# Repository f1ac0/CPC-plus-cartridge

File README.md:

# CPC-plus-cartridge
In this repository you will find different PCB designs and code to make a CPC-plus cartridge. The ACID chip is implemented inside a XC9536XL CPLD using the equations published by octoate : https://www.octoate.de/articles/acid-verilog-code/

Facts about this project :
- The ZIF version has a ZIF socket for DIP32 ROM SST39SF040 or W29C040, and is longer than standard cartridges
- the PLCC version can be used with PLCC SST39SF040 ROMs and its size is more standard
- They both have jumpers to select 128k, 256k or 512K cartridge ROM banks

# Disclaimer
This is a hobbyist project, it comes with no warranty and no support. Also remember that the Amstrad machines are about 30 years old and may fail because of such hardware expansions.

I publish my work under the CC-BY-NC-SA license.

If you find it useful and want to reward me : I am always looking for Amiga/Amstrad CPC hardware to repair and hack, please contact me.

# BOM
- 1x XC9536XL CPLD
- 1x DIP32/PLCC32 ROM SST39SF040 or W29C040 and appropriate socket
- 1x 3.3v LDO, either SPX3819M5-L-3-3 or XC6206P332MR
- 2x 1uF (or more) 0805 capacitors
- 4x 100nF 0805 capacitors

# Making it
Check for shorts at least between 5V, 3.3V, and GND traces before applying power !

The programming port does not need to be soldered since it needs to be programmed just once : you can just hold it in place during the few seconds required for programming.

CPLD code is generated and built into xsvf using Xilinx ISE 14.7 IDE then iMPACT. "Macrocell power setting" can be "Low" an "Slew rate" to "Slow".

There are several methods to program the XC9536XL. I personally use xsvfduino : https://github.com/wschutzer/xsvfduino

Check the alignment between the cartridge pads and connector pads inside the CPC when installing it for the first time.

# Using it
- Burn the ROM images and install the ROM. Do not burn .cpr files directly, they need to be first converted using for example "CPRTools".
- Choose the ROM to use and its size using the jumpers :
  - 512k = both jumpers vertical
  - 256k = "128" jumper vertical and "256" to select 0 or 1
  - 128k = both jumpers to select 0 or 1
- Enjoy

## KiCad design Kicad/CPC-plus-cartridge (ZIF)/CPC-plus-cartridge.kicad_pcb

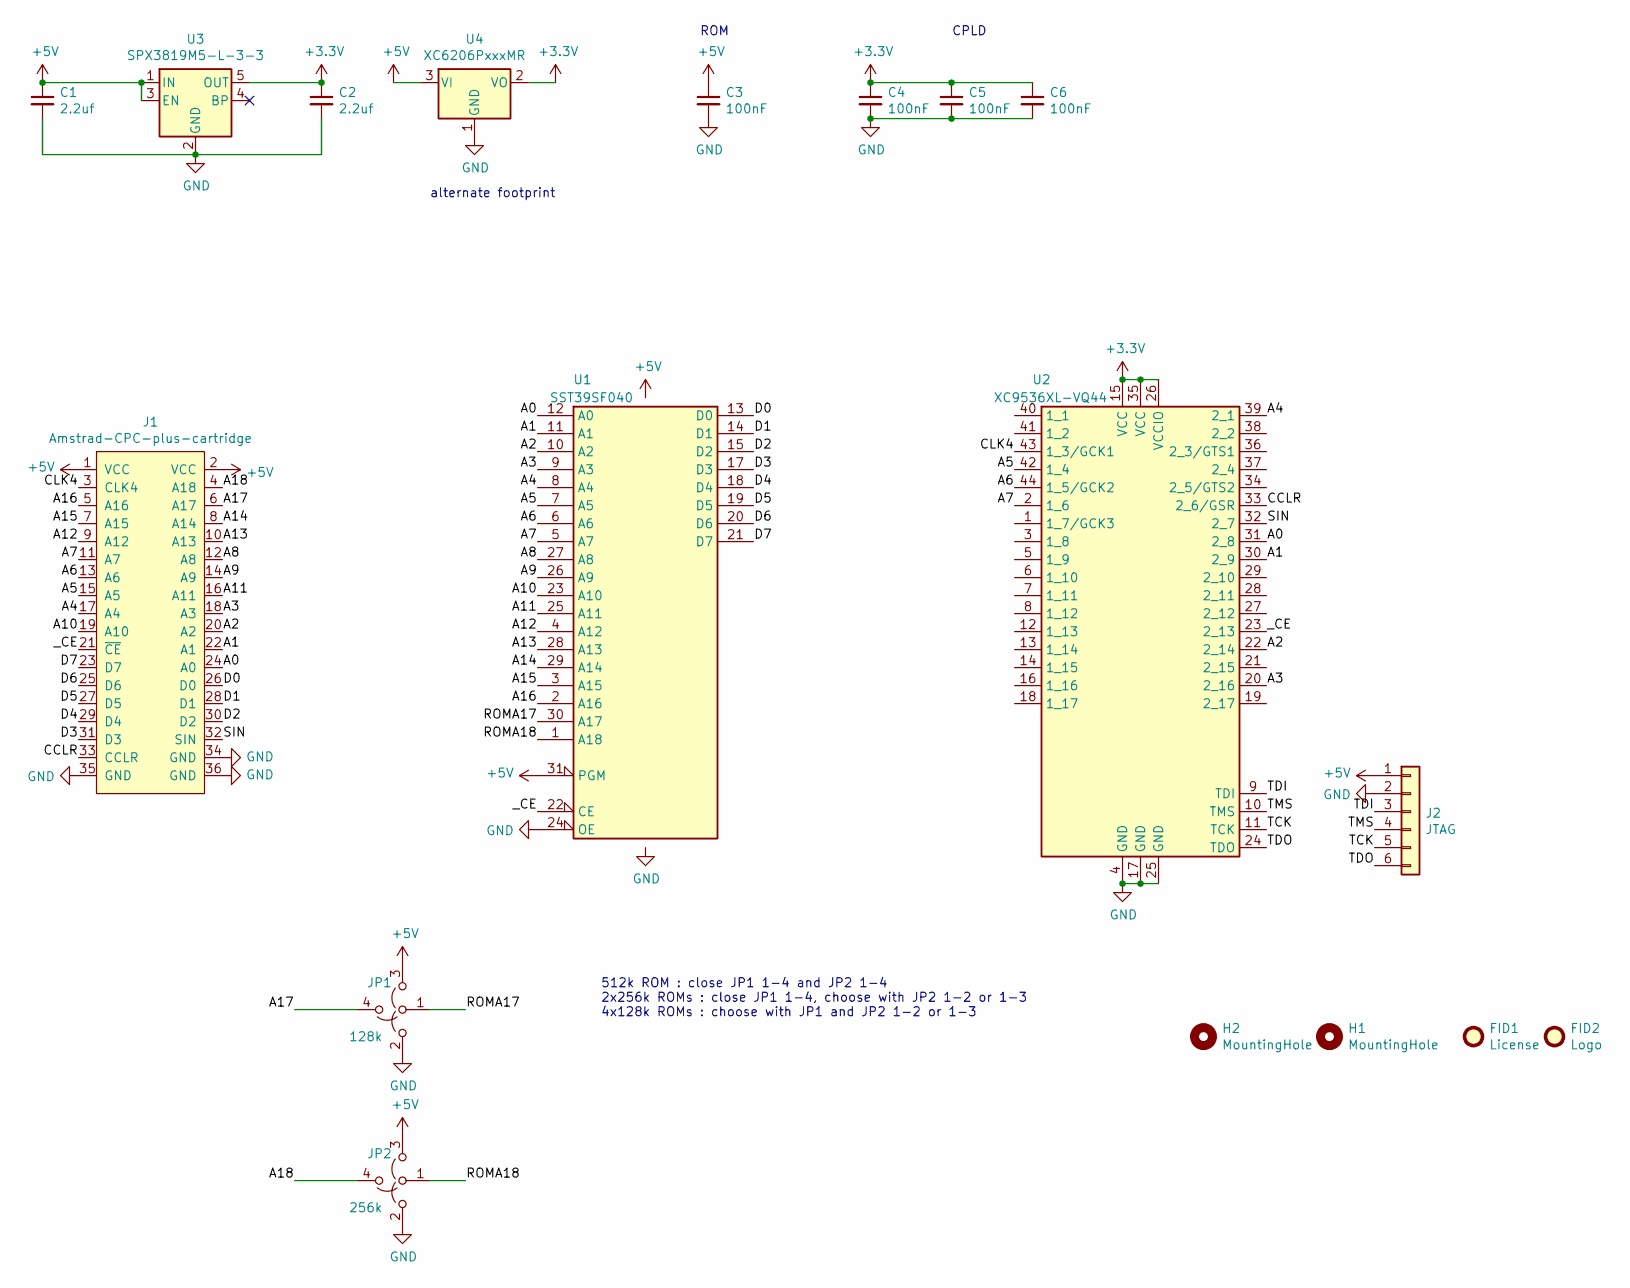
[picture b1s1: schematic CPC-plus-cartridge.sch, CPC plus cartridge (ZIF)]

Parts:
C1, C2: 2.2uf; C_0805_2012Metric
C3, C4, C5, C6: 100nF; C_0805_2012Metric
FID1: License; CC_BY_NC_SA_square_silkscreen
FID2: Logo; PIC_Cassepanards_GS
H1, H2: MountingHole; MountingHole_3mm
J1: Amstrad-CPC-plus-cartridge
J2: JTAG; PinHeader_1x06_P2.54mm_Vertical
JP1: 128k; Jumper_4_SPTT_P2.54mm_Edgemount
JP2: 256k; Jumper_4_SPTT_P2.54mm_Edgemount
U1: SST39SF040; DIP-32_W15.24mm_Socket_1mm
U2: XC9536XL-VQ44; LQFP-44_10x10mm_P0.8mm
U3: SPX3819M5-L-3-3; SOT-23-5
U4: XC6206PxxxMR; SOT-23

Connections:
+3V3: C2.1, C4.1, C5.1, C6.1, U2.15 (VCC), U2.26 (VCCIO), U2.35 (VCC), U3.5 (OUT), U4.2 (VO)
+5V: C1.1, C3.1, J1.1 (VCC), J1.2 (VCC), J2.1, JP1.3 (B), JP2.3 (B), U1.31 (PGM), U1.32 (VCC), U3.1 (IN), U3.3 (EN), U4.3 (VI)
/A0: J1.24 (A0), U1.12 (A0), U2.31 (2_8)
/A1: J1.22 (A1), U1.11 (A1), U2.30 (2_9)
/A2: J1.20 (A2), U1.10 (A2), U2.22 (2_14)
/A3: J1.18 (A3), U1.9 (A3), U2.20 (2_16)
/A4: J1.17 (A4), U1.8 (A4), U2.39 (2_1)
/A5: J1.15 (A5), U1.7 (A5), U2.42 (1_4)
/A6: J1.13 (A6), U1.6 (A6), U2.44 (1_5/GCK2)
/A7: J1.11 (A7), U1.5 (A7), U2.2 (1_6)
/A8: J1.12 (A8), U1.27 (A8)
/A9: J1.14 (A9), U1.26 (A9)
/A10: J1.19 (A10), U1.23 (A10)
/A11: J1.16 (A11), U1.25 (A11)
/A12: J1.9 (A12), U1.4 (A12)
/A13: J1.10 (A13), U1.28 (A13)
/A14: J1.8 (A14), U1.29 (A14)
/A15: J1.7 (A15), U1.3 (A15)
/A16: J1.5 (A16), U1.2 (A16)
/A17: J1.6 (A17), JP1.4 (D)
/A18: J1.4 (A18), JP2.4 (D)
/CCLR: J1.33 (CCLR), U2.33 (2_6/GSR)
/CLK4: J1.3 (CLK4), U2.43 (1_3/GCK1)
/D0: J1.26 (D0), U1.13 (D0)
/D1: J1.28 (D1), U1.14 (D1)
/D2: J1.30 (D2), U1.15 (D2)
/D3: J1.31 (D3), U1.17 (D3)
/D4: J1.29 (D4), U1.18 (D4)
/D5: J1.27 (D5), U1.19 (D5)
/D6: J1.25 (D6), U1.20 (D6)
/D7: J1.23 (D7), U1.21 (D7)
/ROMA17: JP1.1 (A), U1.30 (A17)
/ROMA18: JP2.1 (A), U1.1 (A18)
/SIN: J1.32 (SIN), U2.32 (2_7)
/TCK: J2.5, U2.11 (TCK)
/TDI: J2.3, U2.9 (TDI)
/TDO: J2.6, U2.24 (TDO)
/TMS: J2.4, U2.10 (TMS)
/_CE: J1.21 (~CE~), U1.22 (CE), U2.23 (2_13)
GND: C1.2, C2.2, C3.2, C4.2, C5.2, C6.2, J1.34 (GND), J1.35 (GND), J1.36 (GND), J2.2, JP1.2 (B), JP2.2 (B), U1.16 (GND), U1.24 (OE), U2.4 (GND), U2.17 (GND), U2.25 (GND), U3.2 (GND), U4.1 (GND)

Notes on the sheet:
ROM
CPLD
alternate footprint
512k ROM : close JP1 1-4 and JP2 1-4 2x256k ROMs : close JP1 1-4, choose with JP2 1-2 or 1-3 4x128k ROMs : choose with JP1 and JP2 1-2 or 1-3

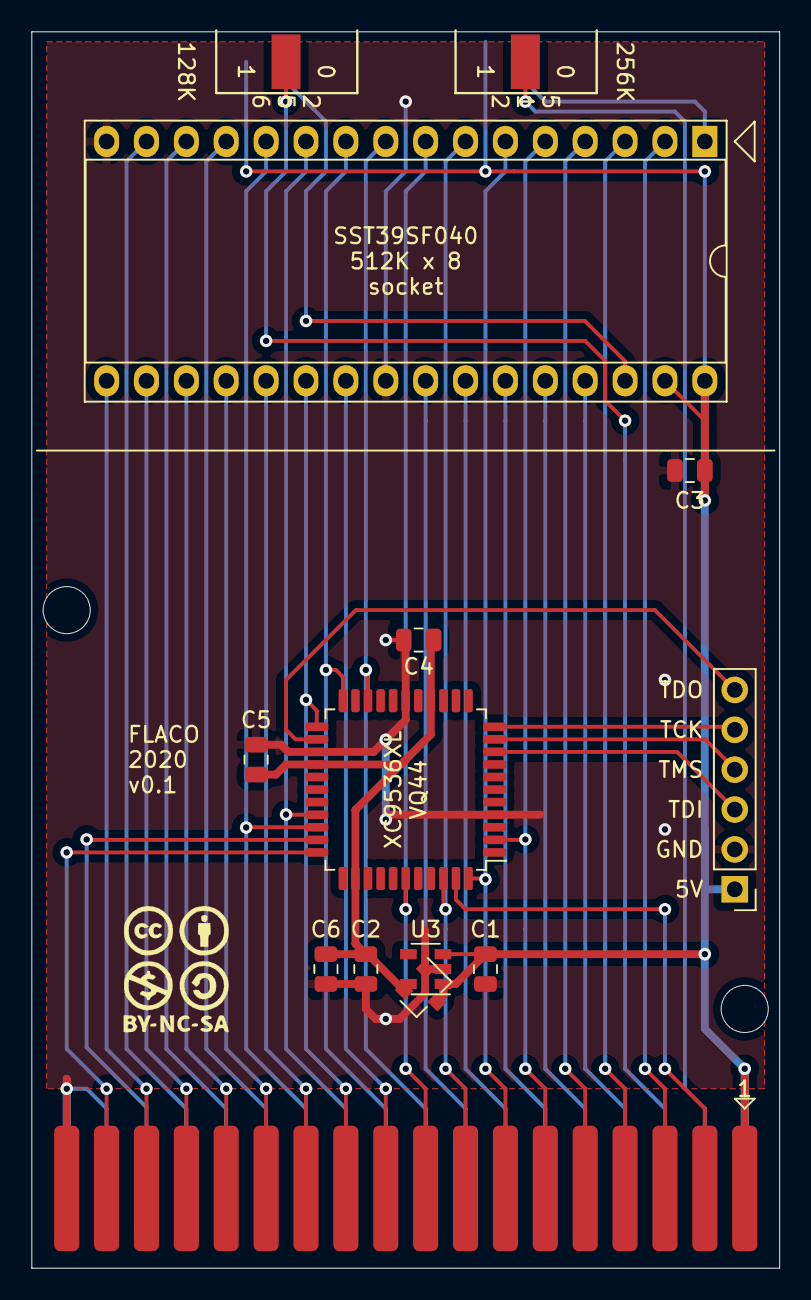
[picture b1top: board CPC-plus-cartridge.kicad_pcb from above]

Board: 2 copper layers, 47.6 x 78.7 mm, 18 parts (1 on the bottom side), 40 nets.

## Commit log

2021-01-19 Respository init with KiCAD files, CPLD, Readme and License
2021-03-06 New KiCAD design for PLCC EPROM
2022-02-15 Photo, InteractiveHtmlBom and README
2023-05-21 Fix 256K jumper instructions

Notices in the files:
Kicad/CPC-plus-cartridge (PLCC)/CPC-plus-cartridge.sch:
FLACO 2019-2020, licence of this schematic is CC-BY-NC-SA
